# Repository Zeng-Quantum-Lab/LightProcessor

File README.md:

PCB program and design for Optical chemical potential mapping processor at Zeng Lab, Purdue University.

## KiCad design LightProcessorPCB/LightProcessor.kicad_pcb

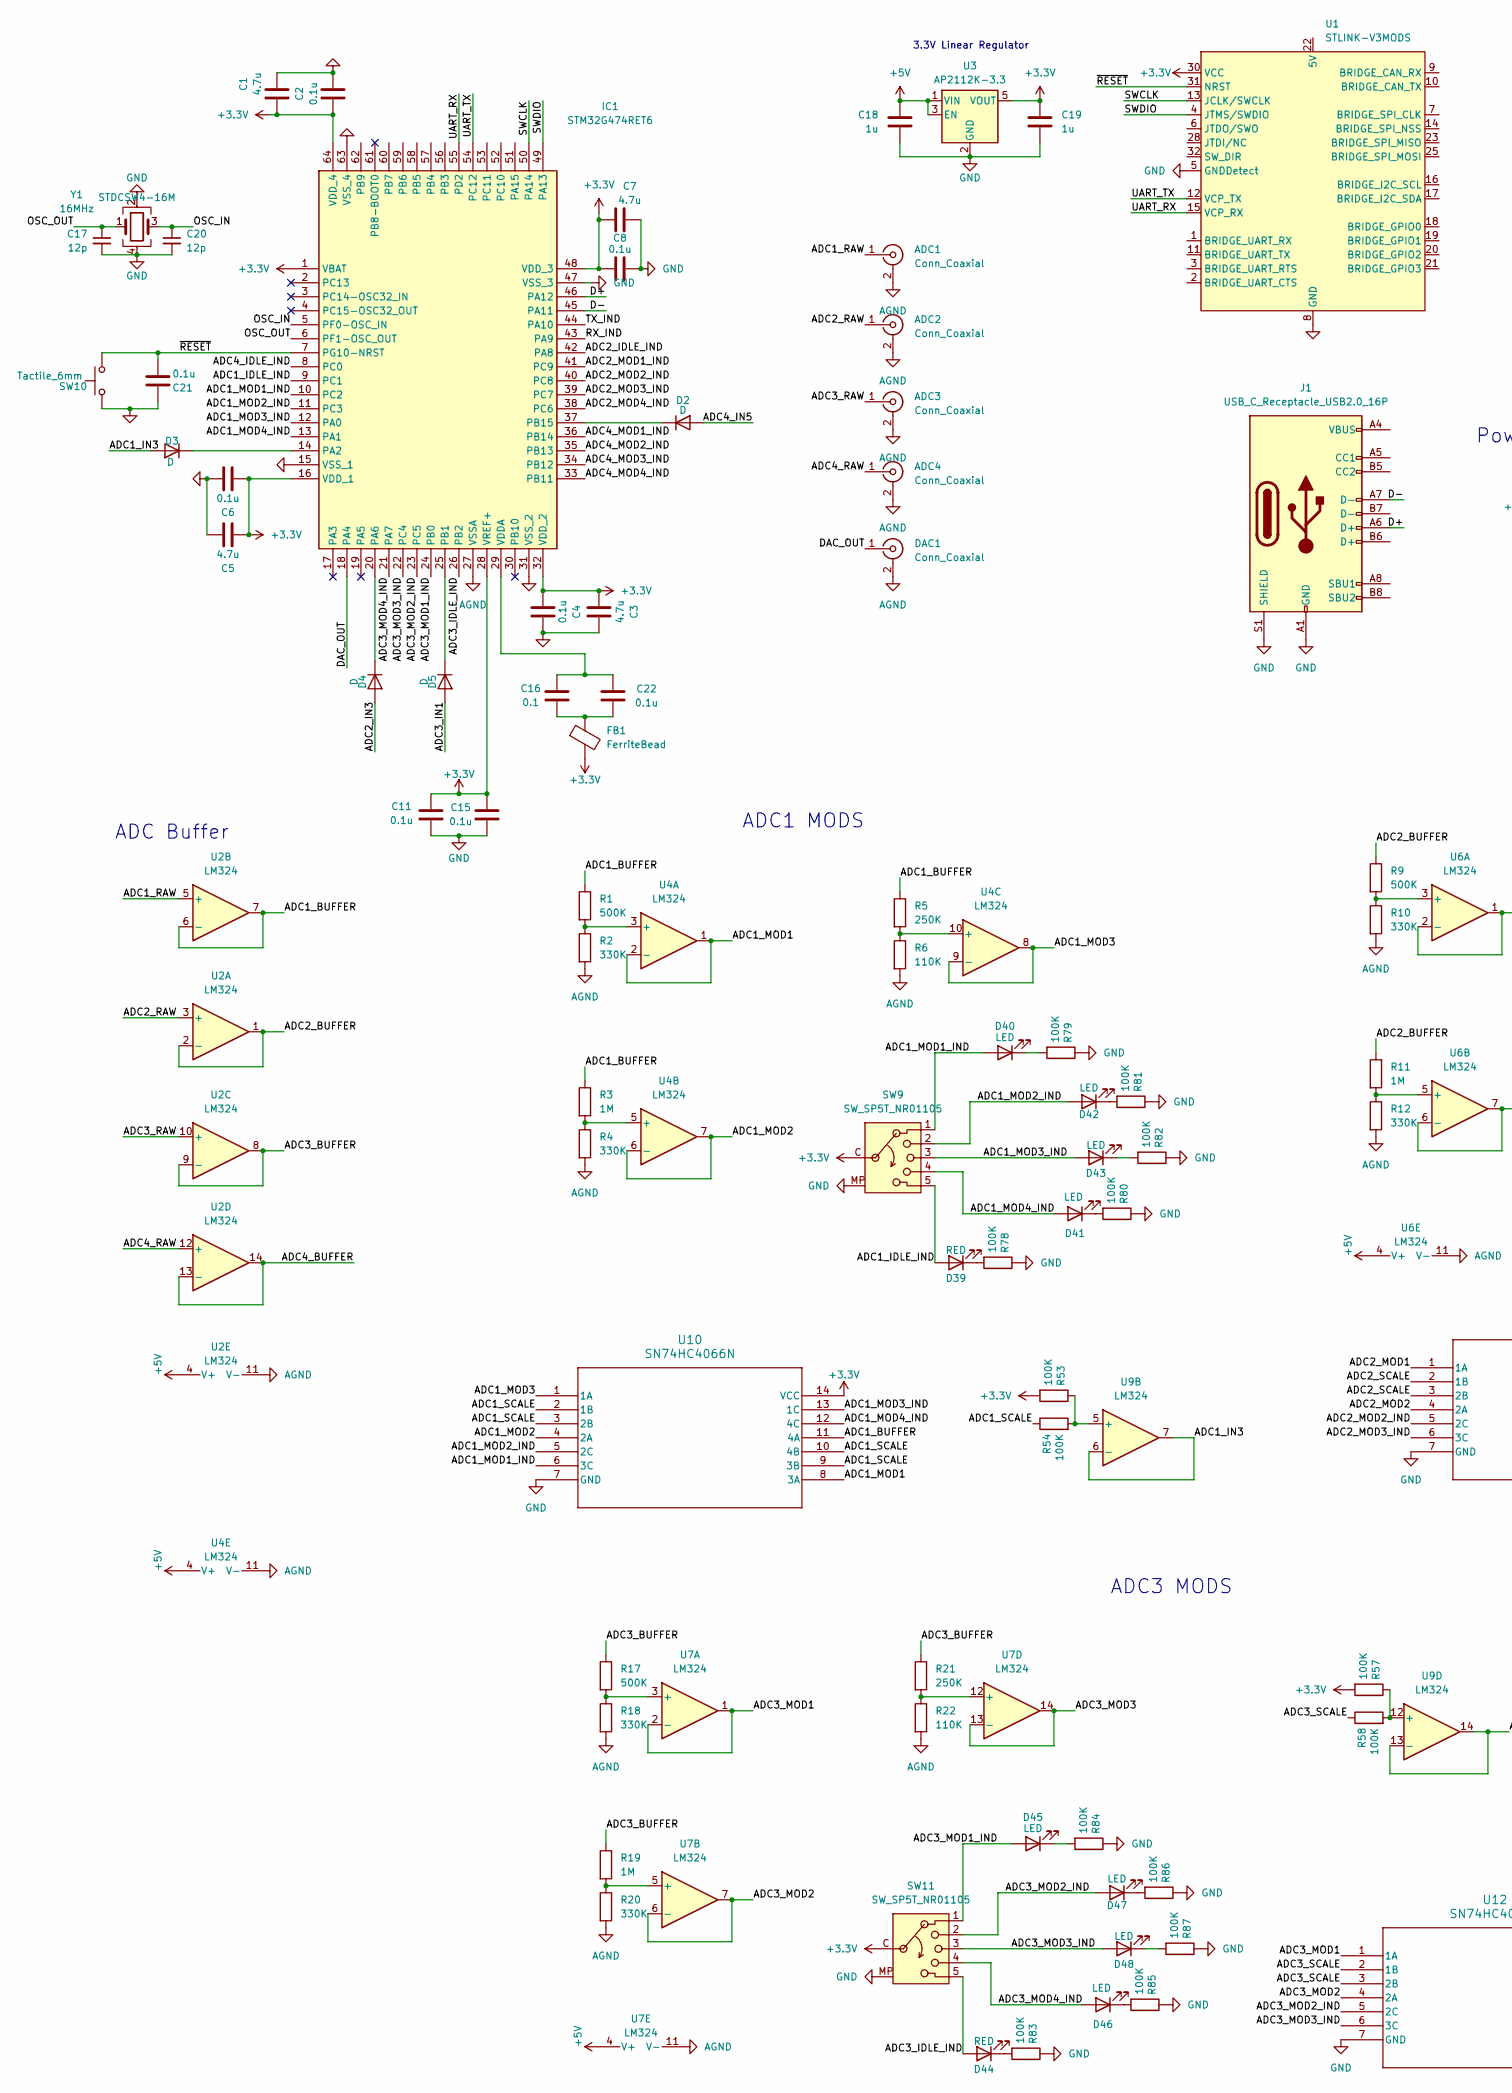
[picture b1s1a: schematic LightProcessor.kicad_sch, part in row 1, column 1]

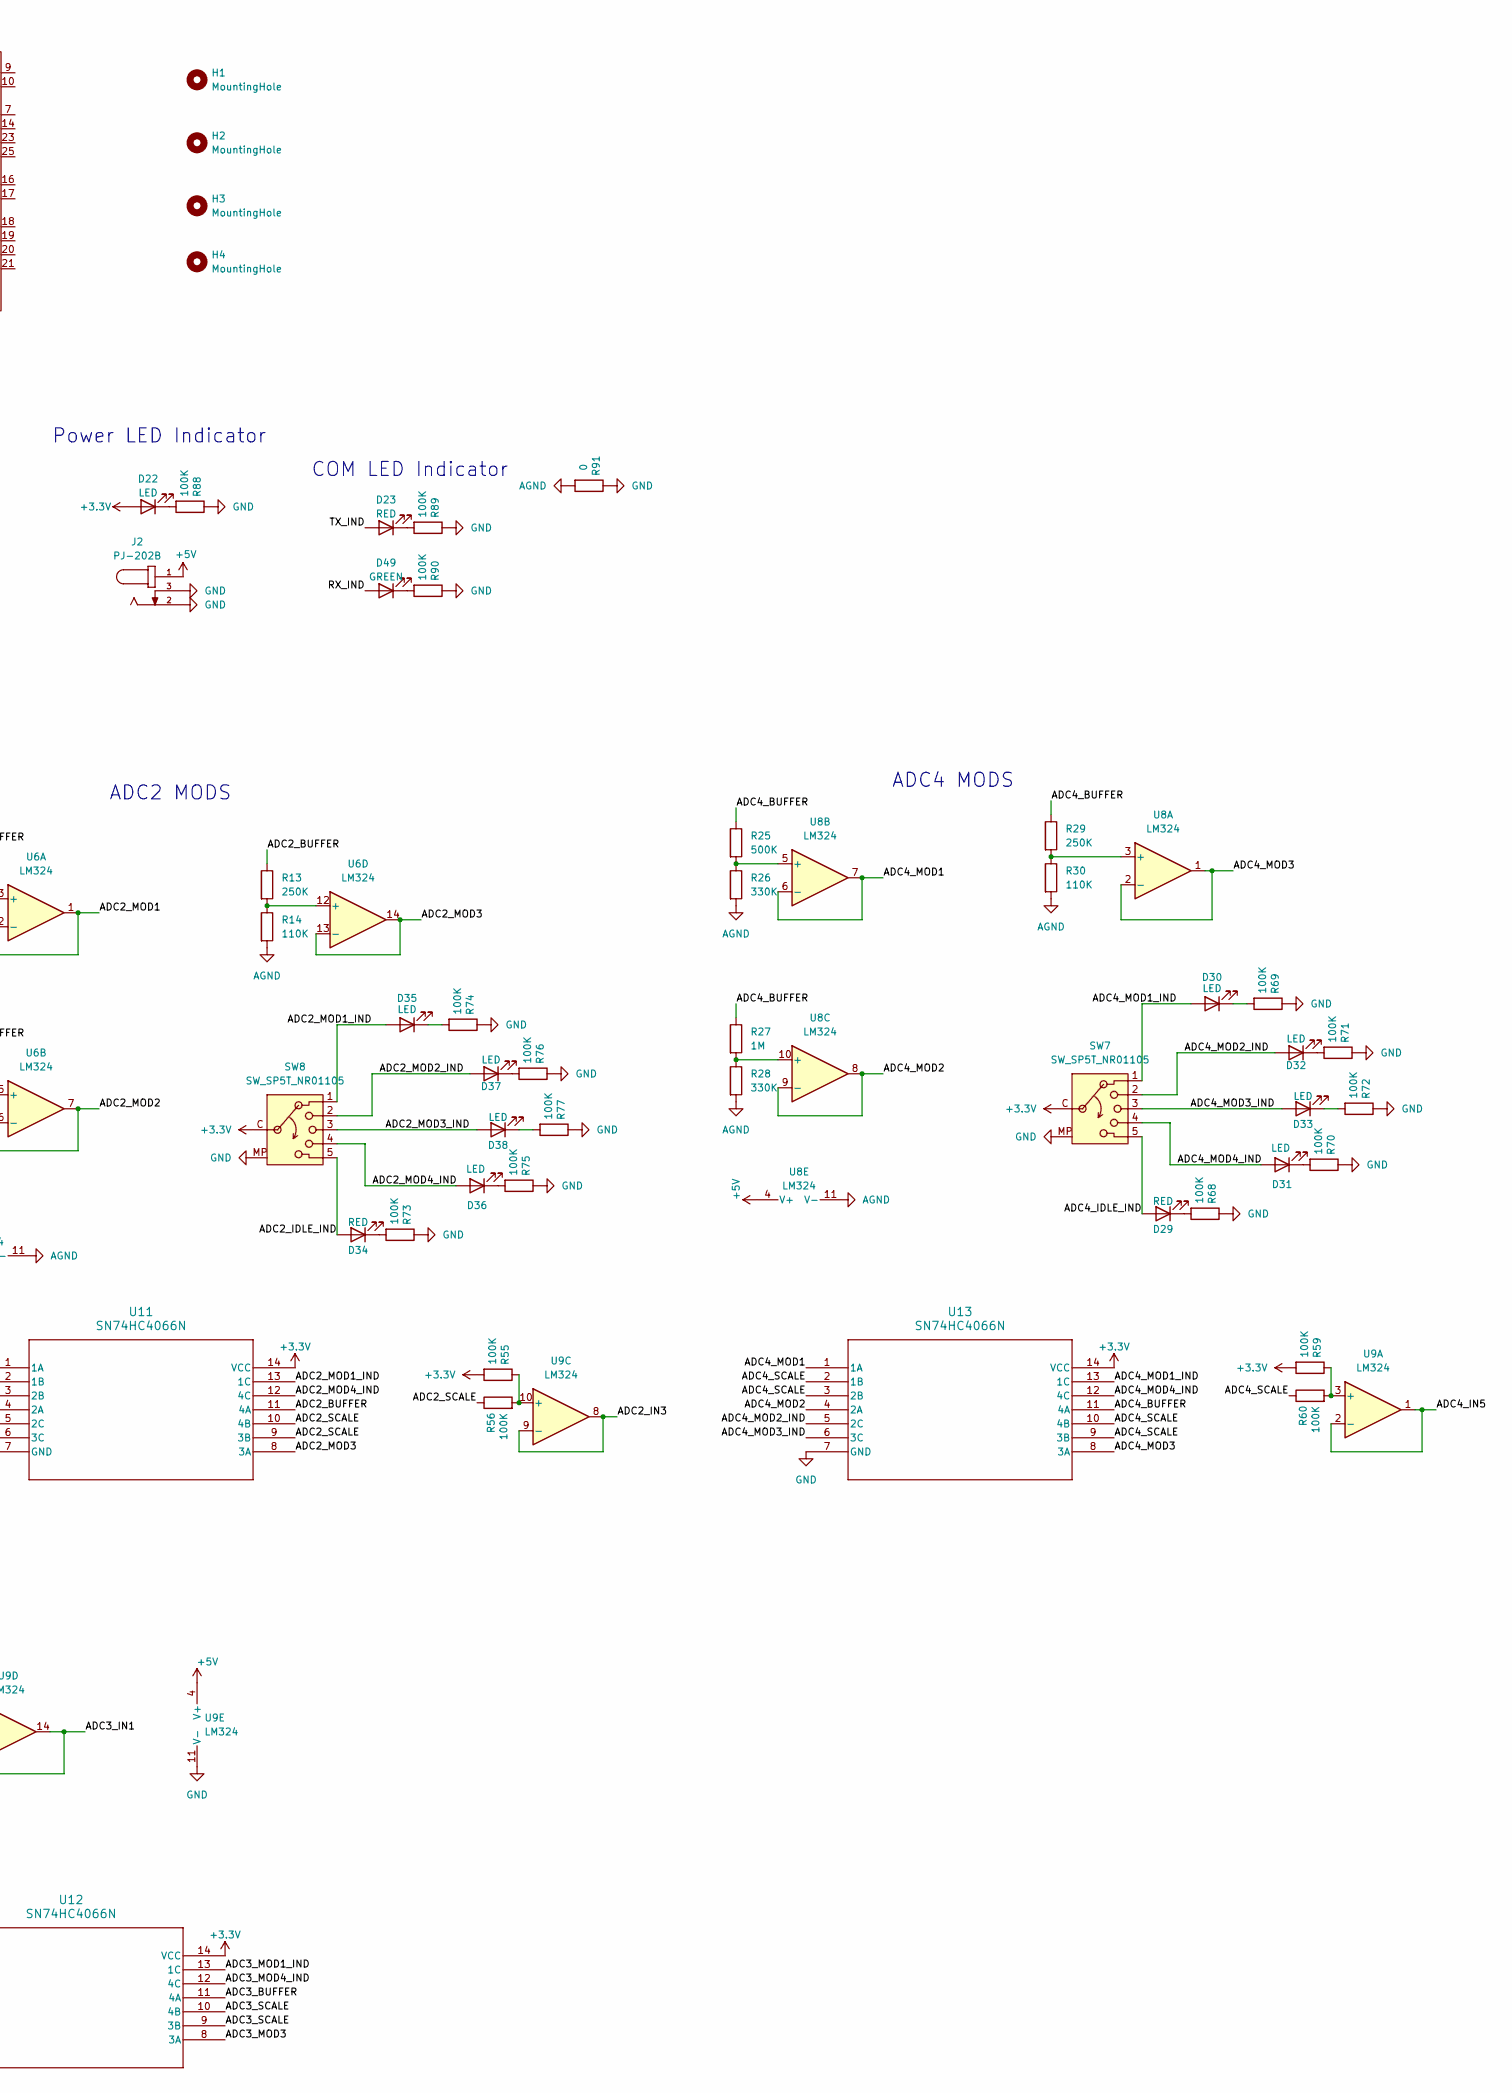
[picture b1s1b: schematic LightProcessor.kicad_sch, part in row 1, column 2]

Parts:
ADC1, ADC2, ADC3, ADC4: Conn_Coaxial; CONN BNC JACK RA 50 OHM PCB
C1, C3, C5, C7: 4.7u; C_0805_2012Metric
C2, C4, C6, C8, C11, C15, C21, C22: 0.1u; C_0805_2012Metric_Pad1.18x1.45mm_HandSolder
C16: 0.1; C_0805_2012Metric_Pad1.18x1.45mm_HandSolder
C17, C20: 12p; C_0805_2012Metric_Pad1.18x1.45mm_HandSolder
C18, C19: 1u; C_0805_2012Metric_Pad1.18x1.45mm_HandSolder
D2, D3, D4, D5: D; D_0805_2012Metric
D22, D30, D31, D32, D33, D35, D36, D37, D38, D40, D41, D42, D43, D45, D46, D47, D48: LED; LED_0805_2012Metric
D23, D29, D34, D39, D44: RED; LED_0805_2012Metric
D49: GREEN; LED_0805_2012Metric
DAC1: Conn_Coaxial; CONN BNC JACK RA 50 OHM PCB
FB1: FerriteBead; C_0805_2012Metric
H1, H2, H3, H4: MountingHole; MountingHole_2.5mm
IC1: STM32G474RET6; QFP50P1200X1200X160-64N; Manufacturer_Part_Number STM32G474RET6; Mouser Part Number 511-STM32G474RET6
J1: USB_C_Receptacle_USB2.0_16P; USB_C_Receptacle_Amphenol_124019772112A
J2: PJ-202B; CUI_PJ-202B; PART_REV 1.02
R1, R9, R17, R25: 500K; R_Axial_DIN0207_L6.3mm_D2.5mm_P15.24mm_Horizontal
R2, R4, R10, R12, R18, R20, R26, R28: 330K; R_Axial_DIN0207_L6.3mm_D2.5mm_P15.24mm_Horizontal
R3, R11, R19, R27: 1M; R_Axial_DIN0207_L6.3mm_D2.5mm_P15.24mm_Horizontal
R5, R13, R21, R29: 250K; R_Axial_DIN0207_L6.3mm_D2.5mm_P15.24mm_Horizontal
R6, R14, R22, R30: 110K; R_Axial_DIN0207_L6.3mm_D2.5mm_P15.24mm_Horizontal
R53, R54, R55, R56, R57, R58, R59, R60, R68, R69, R70, R71, R72, R73, R74, R75, R76, R77, R78, R79, R80, R81, R82, R83, R84, R85, R86, R87, R88, R89, R90: 100K; R_0805_2012Metric
R91: 0; R_0805_2012Metric
SW7, SW8, SW9, SW11: SW_SP5T_NR01105; SW_NKK_NR01
SW10: Tactile_6mm; SW_PUSH_6mm
U1: STLINK-V3MODS; STLink_V3MODS
U2, U4, U6, U7, U8, U9: LM324; DIP825W47P254L1917H533Q14
U3: AP2112K-3.3; SOT-23-5
U10, U11, U12, U13: SN74HC4066N; N14
Y1: 16MHz; Crystal_SMD_2520-4Pin_2.5x2.0mm; Part STDCSW4-16M

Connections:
+3.3V: C1.2, C2.2, C3.2, C4.2, C5.2, C6.2, C7.2, C8.2, C11.1, C15.1, C19.1, D22.2 (A), FB1.2, IC1.1 (VBAT), IC1.16 (VDD_1), IC1.28 (VREF+), IC1.32 (VDD_2), IC1.48 (VDD_3), IC1.64 (VDD_4), R53.2, R55.2, R57.2, R59.2, SW7.C (Common), SW8.C (Common), SW9.C (Common), SW11.C (Common), U1.30 (VCC), U3.5 (VOUT), U10.14 (VCC), U11.14 (VCC), U12.14 (VCC), U13.14 (VCC)
+5V: C18.1, J2.1, U2.4 (V+), U3.1 (VIN), U3.3 (EN), U4.4 (V+), U6.4 (V+), U7.4 (V+), U8.4 (V+), U9.4 (V+)
/ADC1_BUFFER: R1.1, R3.1, R5.1, U2.6 (-), U2.7, U10.11 (4A)
/ADC1_IDLE_IND: D39.2 (A), IC1.9 (PC1), SW9.5
/ADC1_IN3: D3.2 (A), U9.6 (-), U9.7
/ADC1_MOD1: U4.1, U4.2 (-), U10.8 (3A)
/ADC1_MOD1_IND: D40.2 (A), IC1.10 (PC2), SW9.1, U10.6 (3C)
/ADC1_MOD2: U4.6 (-), U4.7, U10.4 (2A)
/ADC1_MOD2_IND: D42.2 (A), IC1.11 (PC3), SW9.2, U10.5 (2C)
/ADC1_MOD3: U4.8, U4.9 (-), U10.1 (1A)
/ADC1_MOD3_IND: D43.2 (A), IC1.12 (PA0), SW9.3, U10.13 (1C)
/ADC1_MOD4_IND: D41.2 (A), IC1.13 (PA1), SW9.4, U10.12 (4C)
/ADC1_RAW: ADC1.1 (In), U2.5 (+)
/ADC1_SCALE: R54.1, U10.2 (1B), U10.3 (2B), U10.9 (3B), U10.10 (4B)
/ADC2_BUFFER: R9.1, R11.1, R13.1, U2.1, U2.2 (-), U11.11 (4A)
/ADC2_IDLE_IND: D34.2 (A), IC1.42 (PA8), SW8.5
/ADC2_IN3: D4.2 (A), U9.8, U9.9 (-)
/ADC2_MOD1: U6.1, U6.2 (-), U11.1 (1A)
/ADC2_MOD1_IND: D35.2 (A), IC1.41 (PC9), SW8.1, U11.13 (1C)
/ADC2_MOD2: U6.6 (-), U6.7, U11.4 (2A)
/ADC2_MOD2_IND: D37.2 (A), IC1.40 (PC8), SW8.2, U11.5 (2C)
/ADC2_MOD3: U6.13 (-), U6.14, U11.8 (3A)
/ADC2_MOD3_IND: D38.2 (A), IC1.39 (PC7), SW8.3, U11.6 (3C)
/ADC2_MOD4_IND: D36.2 (A), IC1.38 (PC6), SW8.4, U11.12 (4C)
/ADC2_RAW: ADC2.1 (In), U2.3 (+)
/ADC2_SCALE: R56.1, U11.2 (1B), U11.3 (2B), U11.9 (3B), U11.10 (4B)
/ADC3_BUFFER: R17.1, R19.1, R21.1, U2.8, U2.9 (-), U12.11 (4A)
/ADC3_IDLE_IND: D44.2 (A), IC1.26 (PB2), SW11.5
/ADC3_IN1: D5.2 (A), U9.13 (-), U9.14
/ADC3_MOD1: U7.1, U7.2 (-), U12.1 (1A)
/ADC3_MOD1_IND: D45.2 (A), IC1.24 (PB0), SW11.1, U12.13 (1C)
/ADC3_MOD2: U7.6 (-), U7.7, U12.4 (2A)
/ADC3_MOD2_IND: D47.2 (A), IC1.23 (PC5), SW11.2, U12.5 (2C)
/ADC3_MOD3: U7.13 (-), U7.14, U12.8 (3A)
/ADC3_MOD3_IND: D48.2 (A), IC1.22 (PC4), SW11.3, U12.6 (3C)
/ADC3_MOD4_IND: D46.2 (A), IC1.21 (PA7), SW11.4, U12.12 (4C)
/ADC3_RAW: ADC3.1 (In), U2.10 (+)
/ADC3_SCALE: R58.1, U12.2 (1B), U12.3 (2B), U12.9 (3B), U12.10 (4B)
/ADC4_BUFFER: R25.1, R27.1, R29.1, U2.13 (-), U2.14, U13.11 (4A)
/ADC4_IDLE_IND: D29.2 (A), IC1.8 (PC0), SW7.5
/ADC4_IN5: D2.2 (A), U9.1, U9.2 (-)
/ADC4_MOD1: U8.6 (-), U8.7, U13.1 (1A)
/ADC4_MOD1_IND: D30.2 (A), IC1.36 (PB14), SW7.1, U13.13 (1C)
/ADC4_MOD2: U8.8, U8.9 (-), U13.4 (2A)
/ADC4_MOD2_IND: D32.2 (A), IC1.35 (PB13), SW7.2, U13.5 (2C)
/ADC4_MOD3: U8.1, U8.2 (-), U13.8 (3A)
/ADC4_MOD3_IND: D33.2 (A), IC1.34 (PB12), SW7.3, U13.6 (3C)
/ADC4_MOD4_IND: D31.2 (A), IC1.33 (PB11), SW7.4, U13.12 (4C)
/ADC4_RAW: ADC4.1 (In), U2.12 (+)
/ADC4_SCALE: R60.1, U13.2 (1B), U13.3 (2B), U13.9 (3B), U13.10 (4B)
/D+: IC1.46 (PA12), J1.A6 (D+)
/D-: IC1.45 (PA11), J1.A7 (D-)
/DAC_OUT: DAC1.1 (In), IC1.18 (PA4)
/OSC_IN: C20.1, IC1.5 (PF0-OSC_IN), Y1.3
/OSC_OUT: C17.1, IC1.6 (PF1-OSC_OUT), Y1.1
/RX_IND: D49.2 (A), IC1.43 (PA9)
/SWCLK: IC1.50 (PA14), U1.13 (JCLK/SWCLK)
/SWDIO: IC1.49 (PA13), U1.4 (JTMS/SWDIO)
/TX_IND: D23.2 (A), IC1.44 (PA10)
/UART_RX: IC1.55 (PD2), U1.15 (VCP_RX)
/UART_TX: IC1.54 (PC12), U1.12 (VCP_TX)
/~RESET: C21.2, IC1.7 (PG10-NRST), SW10.2, U1.31 (NRST)
AGND: ADC1.2 (Ext), ADC2.2 (Ext), ADC3.2 (Ext), ADC4.2 (Ext), DAC1.2 (Ext), IC1.27 (VSSA), R2.2, R4.2, R6.2, R10.2, R12.2, R14.2, R18.2, R20.2, R22.2, R26.2, R28.2, R30.2, R91.2, U2.11 (V-), U4.11 (V-), U6.11 (V-), U7.11 (V-), U8.11 (V-)
GND: C1.1, C2.1, C3.1, C4.1, C5.1, C6.1, C7.1, C8.1, C11.2, C15.2, C17.2, C18.2, C19.2, C20.2, C21.1, IC1.15 (VSS_1), IC1.31 (VSS_2), IC1.47 (VSS_3), IC1.63 (VSS_4), J1.A1 (GND), J1.A12 (GND), J1.B1 (GND), J1.B12 (GND), J1.S1 (SHIELD), J2.2, J2.3, R68.1, R69.1, R70.1, R71.1, R72.1, R73.1, R74.1, R75.1, R76.1, R77.1, R78.1, R79.1, R80.1, R81.1, R82.1, R83.1, R84.1, R85.1, R86.1, R87.1, R88.1, R89.1, R90.1, R91.1, SW7.MP, SW8.MP, SW9.MP, SW10.1, SW11.MP, U1.5 (GNDDetect), U1.8 (GND), U1.24 (GND), U1.26 (GND), U1.27 (GND), U1.29 (GND), U3.2 (GND), U9.11 (V-), U10.7 (GND), U11.7 (GND), U12.7 (GND), U13.7 (GND), Y1.2, Y1.4
unnamed: C16.2, C22.2, FB1.1
unnamed: D2.1 (K), IC1.37 (PB15)
unnamed: D3.1 (K), IC1.14 (PA2)
unnamed: D4.1 (K), IC1.20 (PA6)
unnamed: D5.1 (K), IC1.25 (PB1)
unnamed: D22.1 (K), R88.2
unnamed: D23.1 (K), R89.2
unnamed: D29.1 (K), R68.2
unnamed: D30.1 (K), R69.2
unnamed: D31.1 (K), R70.2
unnamed: D32.1 (K), R71.2
unnamed: D33.1 (K), R72.2
unnamed: D34.1 (K), R73.2
unnamed: D35.1 (K), R74.2
unnamed: D36.1 (K), R75.2
unnamed: D37.1 (K), R76.2
unnamed: D38.1 (K), R77.2
unnamed: D39.1 (K), R78.2
unnamed: D40.1 (K), R79.2
unnamed: D41.1 (K), R80.2
unnamed: D42.1 (K), R81.2
unnamed: D43.1 (K), R82.2
unnamed: D44.1 (K), R83.2
unnamed: D45.1 (K), R84.2
unnamed: D46.1 (K), R85.2
unnamed: D47.1 (K), R86.2
unnamed: D48.1 (K), R87.2
unnamed: D49.1 (K), R90.2
unnamed: C16.1, C22.1, IC1.29 (VDDA)
unnamed: J1.A4 (VBUS), J1.A9 (VBUS), J1.B4 (VBUS), J1.B9 (VBUS)
unnamed: R1.2, R2.1, U4.3 (+)
unnamed: R3.2, R4.1, U4.5 (+)
unnamed: R5.2, R6.1, U4.10 (+)
unnamed: R9.2, R10.1, U6.3 (+)
unnamed: R11.2, R12.1, U6.5 (+)
unnamed: R13.2, R14.1, U6.12 (+)
unnamed: R17.2, R18.1, U7.3 (+)
unnamed: R19.2, R20.1, U7.5 (+)
unnamed: R21.2, R22.1, U7.12 (+)
unnamed: R29.2, R30.1, U8.3 (+)
unnamed: R25.2, R26.1, U8.5 (+)
unnamed: R27.2, R28.1, U8.10 (+)
unnamed: R59.1, R60.2, U9.3 (+)
unnamed: R53.1, R54.2, U9.5 (+)
unnamed: R55.1, R56.2, U9.10 (+)
unnamed: R57.1, R58.2, U9.12 (+)

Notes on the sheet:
3.3V Linear Regulator
ADC1 MODS
ADC4 MODS
ADC2 MODS
Power LED Indicator
COM LED Indicator
ADC Buffer
ADC3 MODS

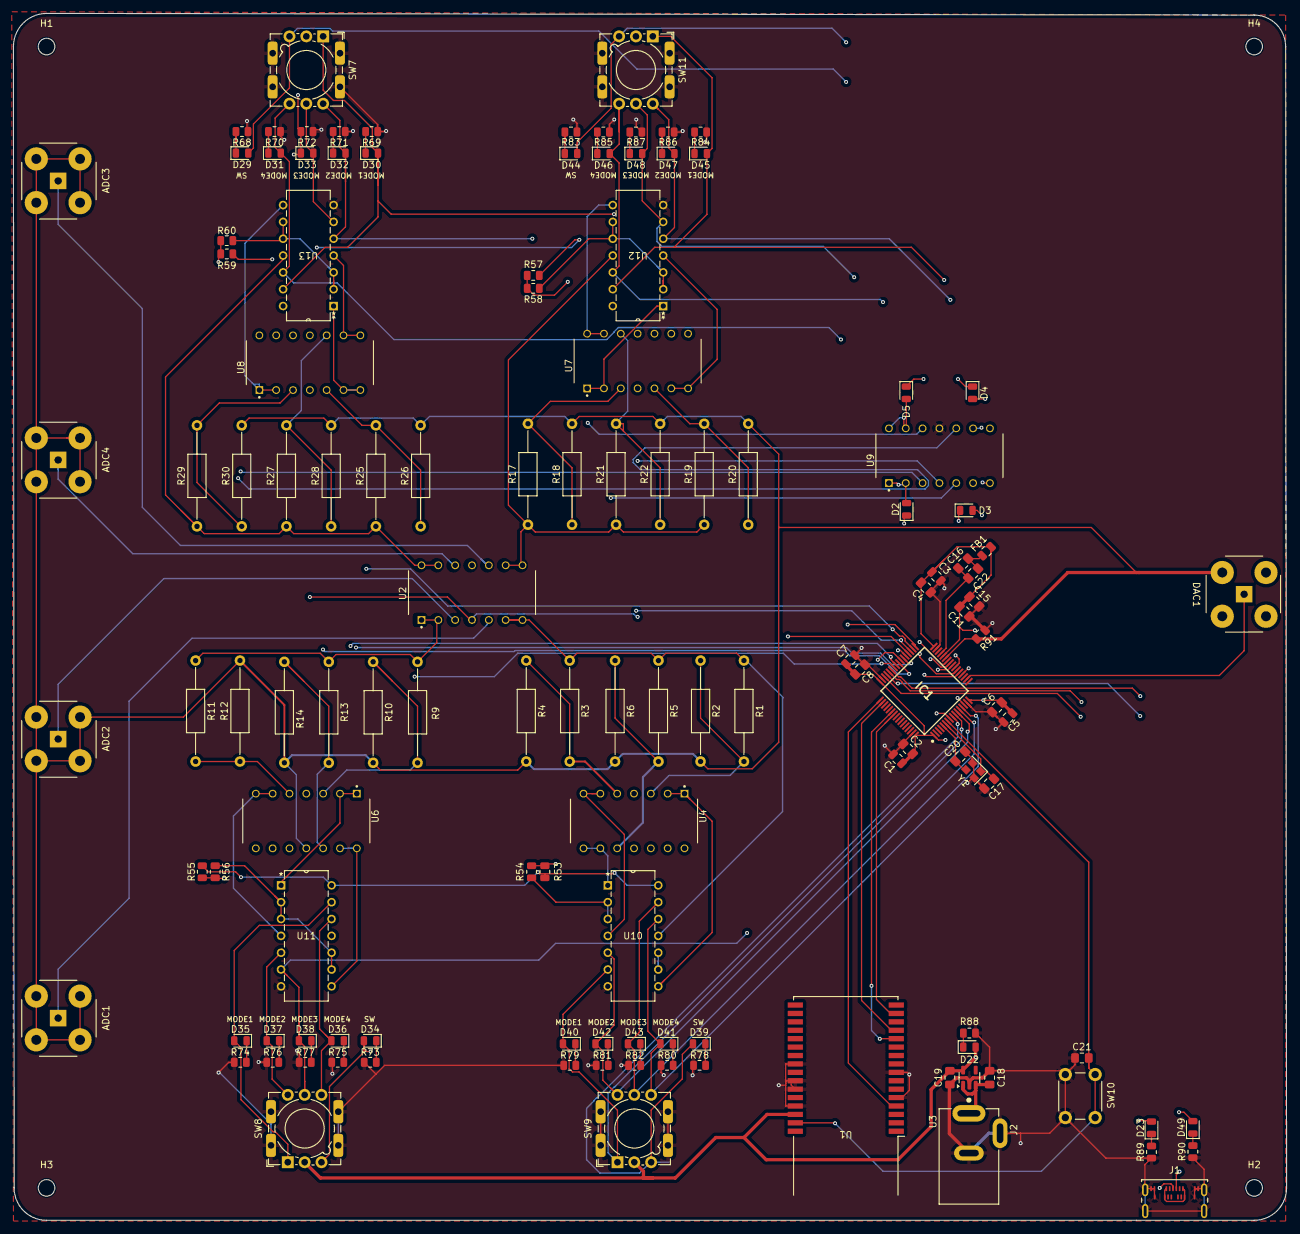
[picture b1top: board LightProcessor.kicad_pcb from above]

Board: 4 copper layers, 192.1 x 182.1 mm, 131 parts (0 on the bottom side), 110 nets.

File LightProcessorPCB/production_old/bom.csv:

Designator,Footprint,Quantity,Value,LCSC Part #
"ADC1, ADC2, ADC3, ADC4, ADC5, DAC1",CONN BNC JACK RA 50 OHM PCB,6,Conn_Coaxial,
"C1, C3, C5, C7",0805,4,4.7u,
"C11, C15, C2, C21, C22, C4, C6, C8",0805,8,0.1u,
C16,0805,1,0.1,
"C17, C20",0805,2,12p,
"C18, C19",0805,2,1u,
"D1, D2, D3, D4, D5",0805,5,D,
"D22, D24, D25, D26, D27, D30, D31, D32, D33, D35, D36, D37, D38, D40, D41, D42, D43, D45, D46, D47, D48",0805,21,LED,
"D23, D28, D29, D34, D39, D44",0805,6,RED,
D49,0805,1,GREEN,
FB1,0805,1,FerriteBead,
IC1,QFP50P1200X1200X160-64N,1,STM32G474RET6,
J1,USB_C_Receptacle_Amphenol_124019772112A,1,USB_C_Receptacle_USB2.0_16P,
J2,CUI_PJ-202B,1,PJ-202B,
"R1, R17, R25, R31, R9",R_Axial_DIN0207_L6.3mm_D2.5mm_P15.24mm_Horizontal,5,500K,
"R10, R12, R18, R2, R20, R26, R28, R32, R34, R4",R_Axial_DIN0207_L6.3mm_D2.5mm_P15.24mm_Horizontal,10,330K,
"R11, R19, R27, R3, R33",R_Axial_DIN0207_L6.3mm_D2.5mm_P15.24mm_Horizontal,5,1M,
"R13, R21, R29, R35, R5",R_Axial_DIN0207_L6.3mm_D2.5mm_P15.24mm_Horizontal,5,250K,
"R14, R22, R30, R36, R6",R_Axial_DIN0207_L6.3mm_D2.5mm_P15.24mm_Horizontal,5,110K,
"R53, R54, R55, R56, R57, R58, R59, R60, R61, R62, R63, R64, R65, R66, R67, R68, R69, R70, R71, R72, R73, R74, R75, R76, R77, R78, R79, R80, R81, R82, R83, R84, R85, R86, R87, R88, R89, R90",0805,38,100K,
SW10,SW_PUSH_6mm,1,Tactile_6mm,
"SW11, SW6, SW7, SW8, SW9",SW_NKK_NR01,5,SW_SP5T_NR01105,
U1,STLink_V3MODS,1,STLINK-V3MODS,
"U10, U11, U12, U13, U14",N14,5,SN74HC4066N,
"U15, U2, U4, U6, U7, U8, U9",DIP825W47P254L1917H533Q14,7,LM324,
U3,SOT-23-5,1,AP2112K-3.3,
Y1,Crystal_SMD_2520-4Pin_2.5x2.0mm,1,16MHz,

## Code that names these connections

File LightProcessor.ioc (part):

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Mcu.Name=STM32G474R(B-C-E)Tx
Mcu.Package=LQFP64
Mcu.UserName=STM32G474RETx
PA0.GPIOParameters=GPIO_PuPd,GPIO_Label
PA0.GPIO_Label=ADC1_MOD3_IND
PA0.GPIO_PuPd=GPIO_PULLDOWN
PA0.Signal=GPIO_Input
PA1.GPIOParameters=GPIO_PuPd,GPIO_Label
PA1.GPIO_Label=ADC1_MOD4_IND
PA1.GPIO_PuPd=GPIO_PULLDOWN
PA1.Signal=GPIO_Input
PA10.GPIOParameters=GPIO_PuPd,GPIO_Label
PA10.GPIO_Label=TX_IND
PA10.GPIO_PuPd=GPIO_PULLDOWN
PA10.Signal=GPIO_Output
PA11.Mode=Device
PA11.Signal=USB_DM
PA12.Mode=Device
PA12.Signal=USB_DP
PA13.Mode=Serial_Wire
PA13.Signal=SYS_JTMS-SWDIO
PA14.Mode=Serial_Wire
PA14.Signal=SYS_JTCK-SWCLK
PA2.Mode=IN3-Single-Ended
PA2.Signal=ADC1_IN3
PA4.Signal=COMP_DAC11_group
PA6.Mode=IN3-Single-Ended
PA6.Signal=ADC2_IN3
PA7.GPIOParameters=GPIO_PuPd,GPIO_Label
PA7.GPIO_Label=ADC_MOD4_IND
PA7.GPIO_PuPd=GPIO_PULLDOWN
PA7.Signal=GPIO_Input
PA8.GPIOParameters=GPIO_PuPd,GPIO_Label
PA8.GPIO_Label=ADC2_IDLE_IND
PA8.GPIO_PuPd=GPIO_PULLDOWN
PA8.Signal=GPIO_Input
PA9.GPIOParameters=GPIO_PuPd,GPIO_Label
PA9.GPIO_Label=RX_IND
PA9.GPIO_PuPd=GPIO_PULLDOWN
PA9.Signal=GPIO_Output
PB0.GPIOParameters=GPIO_PuPd,GPIO_Label
PB0.GPIO_Label=ADC3_MOD1_IND
PB0.GPIO_PuPd=GPIO_PULLDOWN
PB0.Signal=GPIO_Input
PB1.Mode=IN1-Single-Ended
PB1.Signal=ADC3_IN1
PB11.GPIOParameters=GPIO_PuPd,GPIO_Label
PB11.GPIO_Label=ADC4_MOD4_IND
PB11.GPIO_PuPd=GPIO_PULLDOWN
PB11.Signal=GPIO_Input
PB12.GPIOParameters=GPIO_PuPd,GPIO_Label
PB12.GPIO_Label=ADC4_MOD3_IND
PB12.GPIO_PuPd=GPIO_PULLDOWN
PB12.Signal=GPIO_Input
PB13.GPIOParameters=GPIO_PuPd,GPIO_Label
PB13.GPIO_Label=ADC4_MOD2_IND
PB13.GPIO_PuPd=GPIO_PULLDOWN
PB13.Signal=GPIO_Input
PB14.GPIOParameters=GPIO_PuPd,GPIO_Label
PB14.GPIO_Label=ADC4_MOD1_IND
PB14.GPIO_PuPd=GPIO_PULLDOWN
PB14.Signal=GPIO_Input
PB15.Mode=IN5-Single-Ended
PB15.Signal=ADC4_IN5
PB2.GPIOParameters=GPIO_PuPd,GPIO_Label
PB2.GPIO_Label=ADC3_IDLE_IND
PB2.GPIO_PuPd=GPIO_PULLDOWN
PB2.Signal=GPIO_Input
PC0.GPIOParameters=GPIO_PuPd,GPIO_Label
PC0.GPIO_Label=ADC4_IDLE_IND
PC0.GPIO_PuPd=GPIO_PULLDOWN
PC0.Signal=GPIO_Input
PC1.GPIOParameters=GPIO_PuPd,GPIO_Label
PC1.GPIO_Label=ADC1_IDLE_IND
PC1.GPIO_PuPd=GPIO_PULLDOWN
PC1.Signal=GPIO_Input
PC12.Mode=Asynchronous
PC12.Signal=UART5_TX
PC2.GPIOParameters=GPIO_PuPd,GPIO_Label
PC2.GPIO_Label=ADC1_MOD1_IND
PC2.GPIO_PuPd=GPIO_PULLDOWN
PC2.Signal=GPIO_Input
PC3.GPIOParameters=GPIO_PuPd,GPIO_Label
PC3.GPIO_Label=ADC1_MOD2_IND
PC3.GPIO_PuPd=GPIO_PULLDOWN
PC3.Signal=GPIO_Input
PC4.GPIOParameters=GPIO_PuPd,GPIO_Label
PC4.GPIO_Label=ADC_MOD3_IND
PC4.GPIO_PuPd=GPIO_PULLDOWN
PC4.Signal=GPIO_Input
PC5.GPIOParameters=GPIO_PuPd,GPIO_Label
PC5.GPIO_Label=ADC3_MOD2_IND
PC5.GPIO_PuPd=GPIO_PULLDOWN
PC5.Signal=GPIO_Input
PC6.GPIOParameters=GPIO_PuPd,GPIO_Label
PC6.GPIO_Label=ADC2_MOD3_IND
PC6.GPIO_PuPd=GPIO_PULLDOWN
PC6.Signal=GPIO_Input
PC7.GPIOParameters=GPIO_PuPd,GPIO_Label
PC7.GPIO_Label=ADC2_MOD3_IND
PC7.GPIO_PuPd=GPIO_PULLDOWN
PC7.Signal=GPIO_Input
PC8.GPIOParameters=GPIO_PuPd,GPIO_Label
PC8.GPIO_Label=ADC2_MOD2_IND
PC8.GPIO_PuPd=GPIO_PULLDOWN
PC8.Signal=GPIO_Input
PC9.GPIOParameters=GPIO_PuPd,GPIO_Label
PC9.GPIO_Label=ADC2_MOD1_IND
PC9.GPIO_PuPd=GPIO_PULLDOWN
PC9.Signal=GPIO_Input
PD2.Mode=Asynchronous
PD2.Signal=UART5_RX
PF0-OSC_IN.Mode=HSE-External-Oscillator
PF0-OSC_IN.Signal=RCC_OSC_IN
PF1-OSC_OUT.Mode=HSE-External-Oscillator
PF1-OSC_OUT.Signal=RCC_OSC_OUT
RCC.HSE_VALUE=16000000
RCC.SYSCLKFreq_VALUE=170000000
RCC.SYSCLKSource=RCC_SYSCLKSOURCE_PLLCLK
board=custom

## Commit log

2025-05-30 Init
2025-05-30 Added .gitignore
2025-05-30 Update STM32 Project file
2025-06-02 Added additional functions
2025-07-11 Update PCB design
2025-07-11 Update project to work with vscode extension
2025-07-30 Update Workspace
2025-07-30 Update USB lib
2025-07-31 Update Code Base
2025-08-06 Added Usb data packet struct and Usb setup packet struct
2025-08-23 Relocate Stack Pointer
